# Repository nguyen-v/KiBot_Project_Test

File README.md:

<h1 align="center">Board Name</h1>

<p align="center" width="100%">
  
</p>

***

<p align="center">
  
&nbsp; &nbsp; &nbsp; &nbsp;
  
</p>

***

## SPECIFICATIONS

| Parameter | Value | 
| --- | --- |
| Dimensions | 34.0 × 28.0 mm |

***

## DIRECTORY STRUCTURE

    .
    ├─ Computations       # Misc calculations
    ├─ HTML               # HTML files for generated webpage
    ├─ Images             # Pictures and renders
    │
    ├─ kibot_resources    # External resources for KiBot
    │  ├─ colors          # Color theme for KiCad
    │  ├─ fonts           # Fonts used in the project
    │  ├─ scripts         # External scripts used with KiBot
    │  └─ templates       # Templates for KiBot generated reports
    │
    ├─ kibot_yaml         # KiBot YAML config files
    ├─ KiRI               # KiRI (PCB diff viewer) files
    │
    ├─ lib                # KiCad footprint and symbol libraries
    │  ├─ 3d_models       # Component 3D models
    │  ├─ lib_fp          # Footprint libraries
    │  └─ lib_sym         # Symbol libraries
    │
    ├─ Logos              # Logos
    │
    ├─ Manufacturing      # Assembly and fabrication documents
    │  ├─ Assembly        # Assembly documents (BoM, pos, notes)
    │  │
    │  └─ Fabrication     # Fabrication documents (ZIP, notes)
    │     ├─ Drill Tables # CSV drill tables
    │     └─ Gerbers      # Gerbers
    │
    ├─ Report             # Reports for ERC/DRC
    ├─ Schematic          # PDF of schematic
    ├─ Templates          # Title block templates
    ├─ Testing
    │  └─ Testpoints      # Testpoints tables      
    │
    └─ Variants           # Outputs for assembly variants

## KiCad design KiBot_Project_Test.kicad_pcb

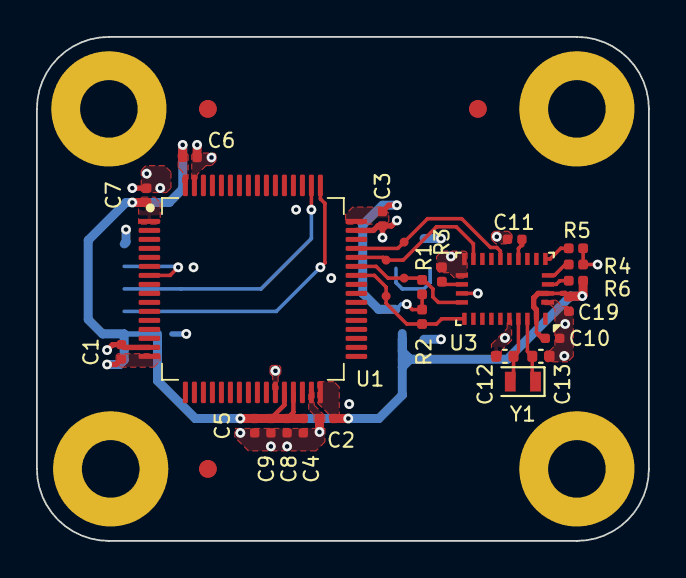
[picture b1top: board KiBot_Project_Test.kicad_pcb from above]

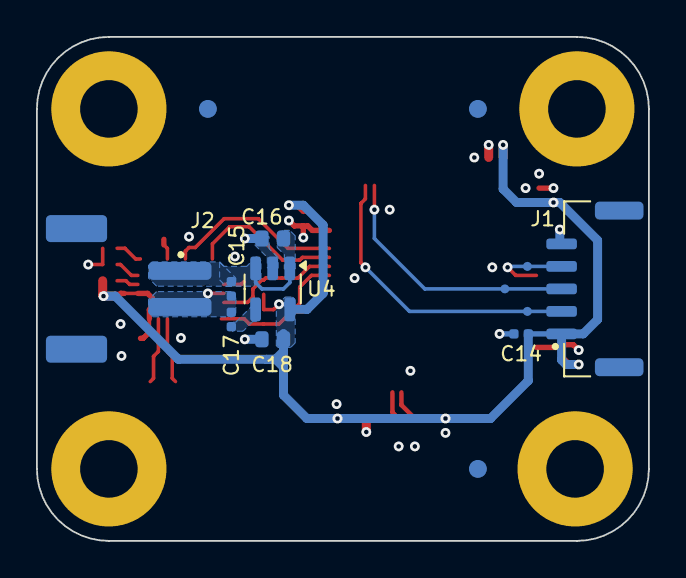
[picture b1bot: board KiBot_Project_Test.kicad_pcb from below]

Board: 4 copper layers, 34.0 x 28.0 mm, 50 parts (16 on the bottom side), 18 nets.

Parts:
C1, C2, C3, C6, C8, C9, C10, C11, C14, C15, C19: 100n X7R 50V; C_0402_1005_DensityHigh
C4, C7: 1u X7R 10V; C_0402_1005_DensityHigh
C5: 4u7 X5R 25V; C_0402_1005_DensityHigh
C12, C13: 3.9pF; C_0402_1005Metric
C16: 1u X7R 25V; C_0603_1608_DensityHigh
C17: 10n X7R 100V; C_0402_1005_DensityHigh
C18: 4u7 X7R 16V; C_0603_1608_DensityHigh
FD1, FD2, FD3, FD4, FD5, FD6: Fiducial; Fiducial_1mm_Mask2mm
H1, H2, H3, H4: M3; MountingHole_3.2mm_M3_Pad
J1: SM05B-GHS-TB; JST_GH_SM05B-GHS-TB_1x05-1MP_P1.25mm_Horizontal
J2: S2B-PH-SM4-TB; JST_PH_S2B-PH-SM4-TB_1x02-1MP_P2.00mm_Horizontal
R1, R2: 2k 1%; R_0402_1005_DensityHigh
R3, R4, R5, R6: 10k 1%; R_0402_1005_DensityHigh
TP1, TP2, TP3, TP4, TP5, TP6, TP7, TP8, TP9: TestPoint; TestPoint_Pad_D0.5mm
U1: STM32G474RET3; LQFP-64_10x10mm_P0.5mm
U3: BNO055; LGA-28_5.2x3.8mm_P0.5mm
U4: LP2992IM5-3.3/NOPB; SOT-23-5
Y1: ECS-.327-7-12-C-TR9; Crystal_SMD_2012-2Pin_2.0x1.2mm

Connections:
+3V3: C1.1, C2.1, C3.1, C4.1, C5.1, C6.1, C7.1, C8.1, C9.1, C10.1, C14.1, C18.1, C19.1, J1.1, R1.1, R2.1, R6.1, TP8.1, U1.1 (VBAT), U1.16 (VDD), U1.28 (VREF+), U1.29 (VDDA), U1.32 (VDD), U1.48 (VDD), U1.64 (VDD), U3.3 (VDD), U3.28 (VDDIO), U4.5 (VOUT)
/Project Architecture/Connectors/ADJ: C17.1, U4.4 (ADJ)
/Project Architecture/Connectors/NRST: J1.4, TP7.1, U1.7 (PG10)
/Project Architecture/Connectors/SWCLK: J1.3, TP6.1, U1.50 (PA14)
/Project Architecture/Connectors/SWDIO: J1.2, TP5.1, U1.49 (PA13)
/Project Architecture/IMU/BLP: R6.2, U3.4 (~BOOT_LOAD_PIN)
/Project Architecture/IMU/CAP: C11.1, U3.9 (CAP)
/Project Architecture/IMU/COM3: R3.1, U3.17 (COM3)
/Project Architecture/IMU/I2C2_SCL: R1.2, TP4.1, U1.43 (PA9), U3.19 (COM1)
/Project Architecture/IMU/I2C2_SDA: R2.2, TP3.1, U1.42 (PA8), U3.20 (COM0)
/Project Architecture/IMU/IMU_INT: TP1.1, U1.44 (PA10), U3.14 (INT)
/Project Architecture/IMU/IMU_~RESET: TP2.1, U1.45 (PA11), U3.11 (~RESET)
/Project Architecture/IMU/PS0: R5.1, U3.6 (PS0)
/Project Architecture/IMU/PS1: R4.1, U3.5 (PS1)
/Project Architecture/IMU/XIN32: C13.1, U3.27 (XIN32), Y1.1
/Project Architecture/IMU/XOUT32: C12.1, U3.26 (XOUT32), Y1.2
GND: C1.2, C2.2, C3.2, C4.2, C5.2, C6.2, C7.2, C8.2, C9.2, C10.2, C11.2, C12.2, C13.2, C14.2, C15.2, C16.2, C17.2, C18.2, C19.2, H1.1, H2.1, H3.1, H4.1, J1.5, J2.2, R3.2, R4.2, R5.2, TP9.1, U1.15 (VSS), U1.27 (VSSA), U1.31 (VSS), U1.47 (VSS), U1.63 (VSS), U3.2 (GND), U3.15 (GNDIO), U3.16 (GNDIO), U3.18 (COM2), U3.25 (GNDIO), U4.2 (GND)
VBUS: C15.1, C16.1, J2.1, U4.1 (VIN), U4.3 (ON/~OFF)

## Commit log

2025-01-21 First draft of schematic
2025-01-21 Update Outputs
2025-01-24 [Schematic][Added] Mounting holes, Testpoints, Fiducials
2025-03-02 [PCB/Sch] Preliminary PCB layout
2025-03-02 [PCB] Checked version
2025-03-02 Update CHANGELOG
2025-03-02 Update Outputs (release)
2025-03-02 Moved SWCLK trace
2025-03-02 Moved the SWCLK trace
